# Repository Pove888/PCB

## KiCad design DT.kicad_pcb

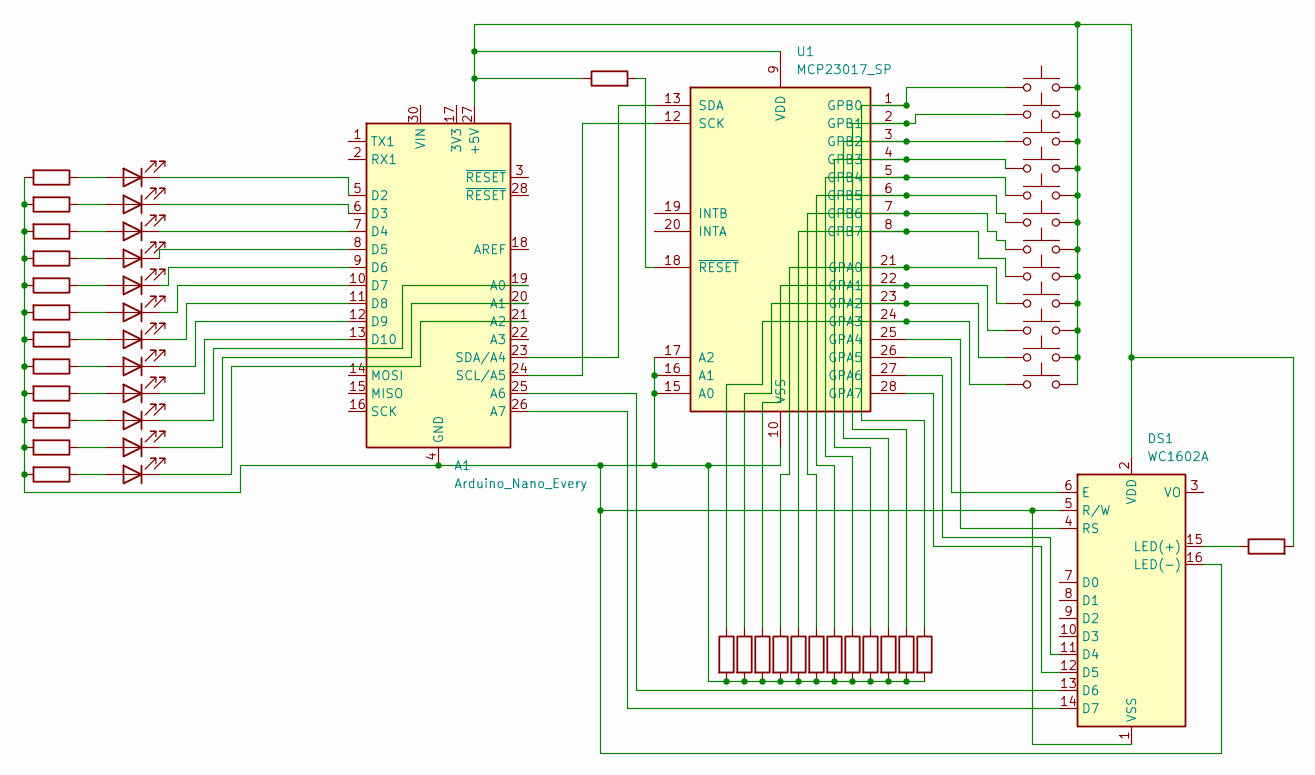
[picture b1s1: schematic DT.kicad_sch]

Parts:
A1: Arduino_Nano_Every; Arduino_Nano
D1, D2, D3, D4, D5, D6, D7, D8, D9, D10, D11, D12: LED; LED_D3.0mm
DS1: WC1602A
R1, R2, R3, R4, R5, R6, R7, R8, R9, R10, R11, R12, R13, R14, R15, R16, R17, R18, R19, R20, R21, R22, R23, R24, R25, R26: R; R_Axial_DIN0204_L3.6mm_D1.6mm_P5.08mm_Horizontal
SW1, SW2, SW3, SW4, SW5, SW6, SW7, SW8, SW9, SW10, SW11, SW12: SW_Push; SW_Cherry_MX_1.00u_PCB
U1: MCP23017_SP; DIP-28_W7.62mm

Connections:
unnamed: A1.27 (+5V), DS1.2 (VDD), R25.2, R26.1, SW1.2, SW2.2, SW3.2, SW4.2, SW5.2, SW6.2, SW7.2, SW8.2, SW9.2, SW10.2, SW11.2, SW12.2, U1.9 (VDD)
unnamed: A1.19 (A0), D3.1 (K)
unnamed: A1.20 (A1), D2.1 (K)
unnamed: A1.21 (A2), D1.1 (K)
unnamed: A1.25 (A6), DS1.13 (D6)
unnamed: A1.26 (A7), DS1.14 (D7)
unnamed: A1.5 (D2), D12.1 (K)
unnamed: A1.6 (D3), D11.1 (K)
unnamed: A1.7 (D4), D10.1 (K)
unnamed: A1.8 (D5), D9.1 (K)
unnamed: A1.9 (D6), D8.1 (K)
unnamed: A1.10 (D7), D7.1 (K)
unnamed: A1.11 (D8), D6.1 (K)
unnamed: A1.12 (D9), D5.1 (K)
unnamed: A1.13 (D10), D4.1 (K)
unnamed: A1.24 (SCL/A5), U1.12 (SCK)
unnamed: A1.23 (SDA/A4), U1.13 (SDA)
unnamed: D1.2 (A), R1.1
unnamed: D2.2 (A), R2.1
unnamed: D3.2 (A), R3.1
unnamed: D4.2 (A), R4.1
unnamed: D5.2 (A), R5.1
unnamed: D6.2 (A), R6.1
unnamed: D7.2 (A), R7.1
unnamed: D8.2 (A), R8.1
unnamed: D9.2 (A), R9.1
unnamed: D10.2 (A), R10.1
unnamed: D11.2 (A), R11.1
unnamed: D12.2 (A), R12.1
unnamed: DS1.11 (D4), U1.27 (GPA6)
unnamed: DS1.12 (D5), U1.28 (GPA7)
unnamed: DS1.6 (E), U1.26 (GPA5)
unnamed: DS1.15 (LED(+)), R25.1
unnamed: A1.4 (GND), A1.29 (GND), DS1.1 (VSS), DS1.5 (R/W), DS1.16 (LED(-)), R1.2, R2.2, R3.2, R4.2, R5.2, R6.2, R7.2, R8.2, R9.2, R10.2, R11.2, R12.2, R13.2, R14.2, R15.2, R16.2, R17.2, R18.2, R19.2, R20.2, R21.2, R22.2, R23.2, R24.2, U1.10 (VSS), U1.15 (A0), U1.16 (A1), U1.17 (A2)
unnamed: DS1.4 (RS), U1.25 (GPA4)
unnamed: R16.1, SW9.1, U1.21 (GPA0)
unnamed: R15.1, SW10.1, U1.22 (GPA1)
unnamed: R14.1, SW11.1, U1.23 (GPA2)
unnamed: R13.1, SW12.1, U1.24 (GPA3)
unnamed: R23.1, SW1.1, U1.1 (GPB0)
unnamed: R18.1, SW2.1, U1.2 (GPB1)
unnamed: R24.1, SW3.1, U1.3 (GPB2)
unnamed: R19.1, SW4.1, U1.4 (GPB3)
unnamed: R20.1, SW5.1, U1.5 (GPB4)
unnamed: R21.1, SW6.1, U1.6 (GPB5)
unnamed: R22.1, SW7.1, U1.7 (GPB6)
unnamed: R17.1, SW8.1, U1.8 (GPB7)
unnamed: R26.2, U1.18 (~RESET)

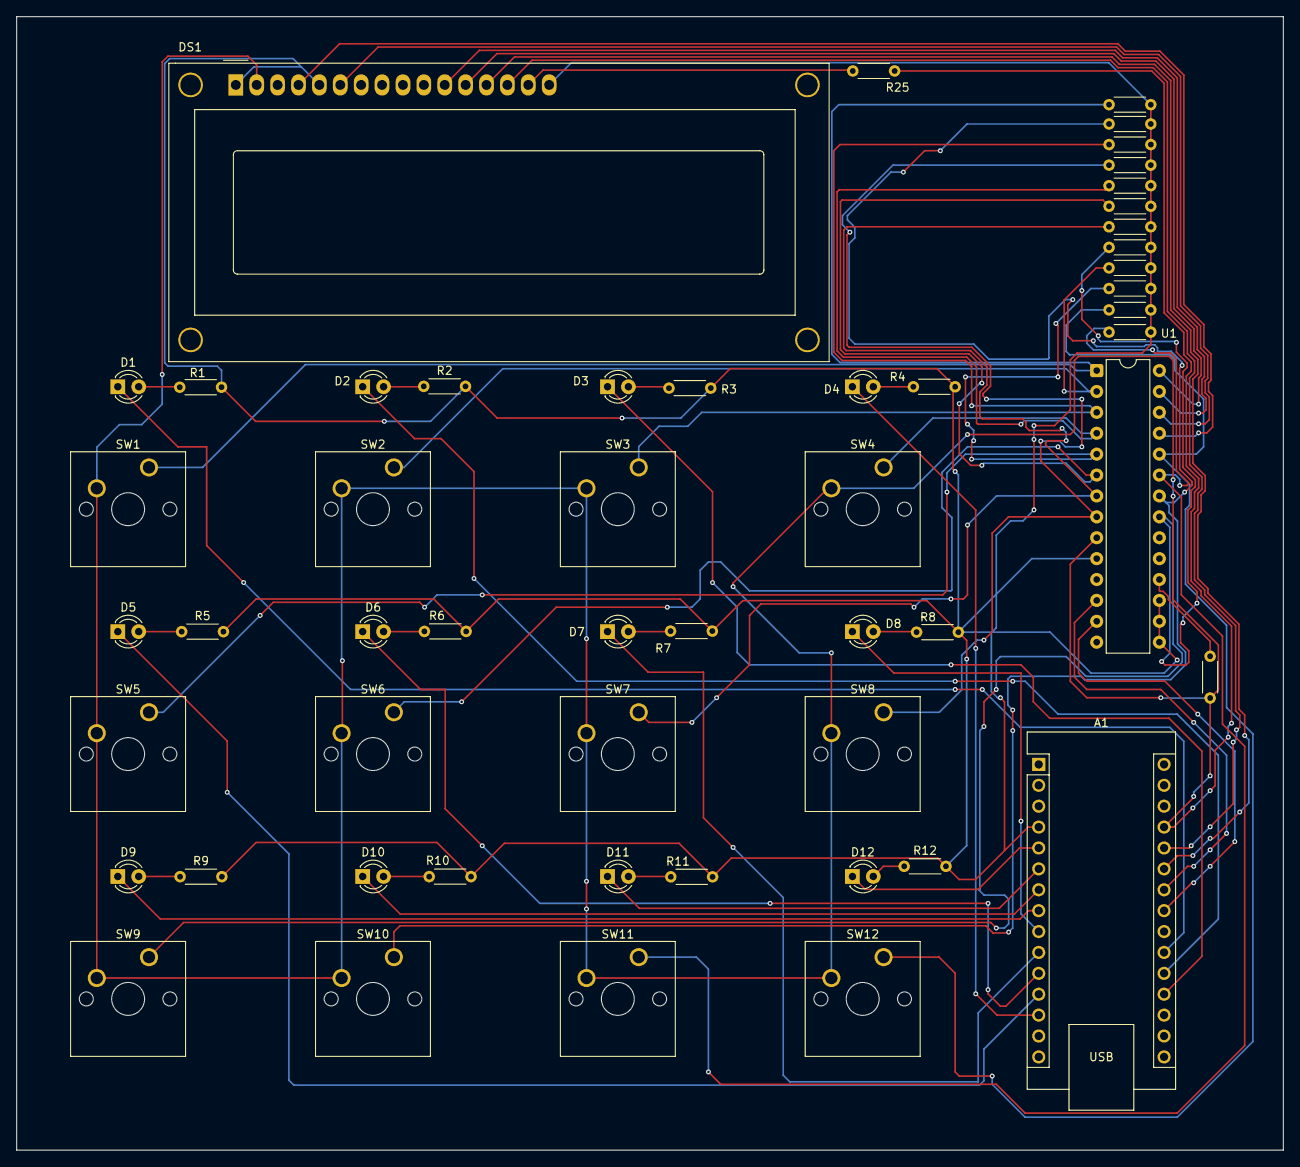
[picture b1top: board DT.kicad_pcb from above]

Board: 2 copper layers, 154.0 x 137.8 mm, 53 parts (0 on the bottom side), 48 nets.

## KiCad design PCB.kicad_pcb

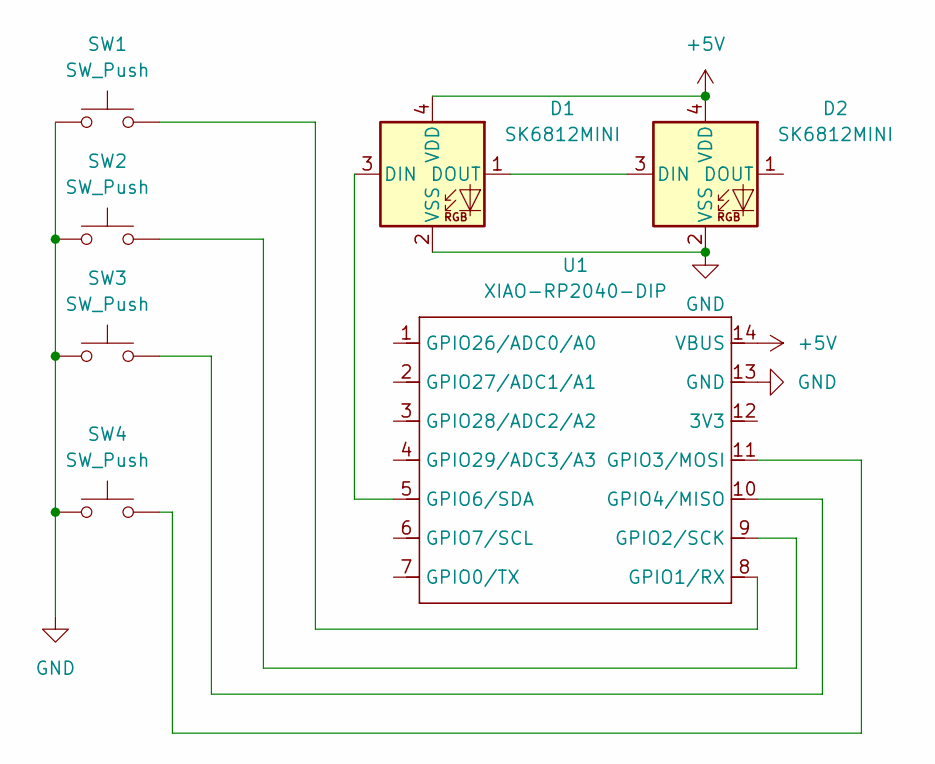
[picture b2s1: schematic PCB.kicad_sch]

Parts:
D1, D2: SK6812MINI; LED_SK6812MINI_PLCC4_3.5x3.5mm_P1.75mm
SW1, SW2, SW3, SW4: SW_Push; SW_Cherry_MX_1.00u_PCB
U1: XIAO-RP2040-DIP

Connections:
+5V: D1.4 (VDD), D2.4 (VDD), U1.14 (VBUS)
GND: D1.2 (VSS), D2.2 (VSS), SW1.1, SW2.1, SW3.1, SW4.1, U1.13 (GND)
unnamed: D1.3 (DIN), U1.5 (GPIO6/SDA)
unnamed: D1.1 (DOUT), D2.3 (DIN)
unnamed: SW1.2, U1.8 (GPIO1/RX)
unnamed: SW2.2, U1.9 (GPIO2/SCK)
unnamed: SW4.2, U1.11 (GPIO3/MOSI)
unnamed: SW3.2, U1.10 (GPIO4/MISO)

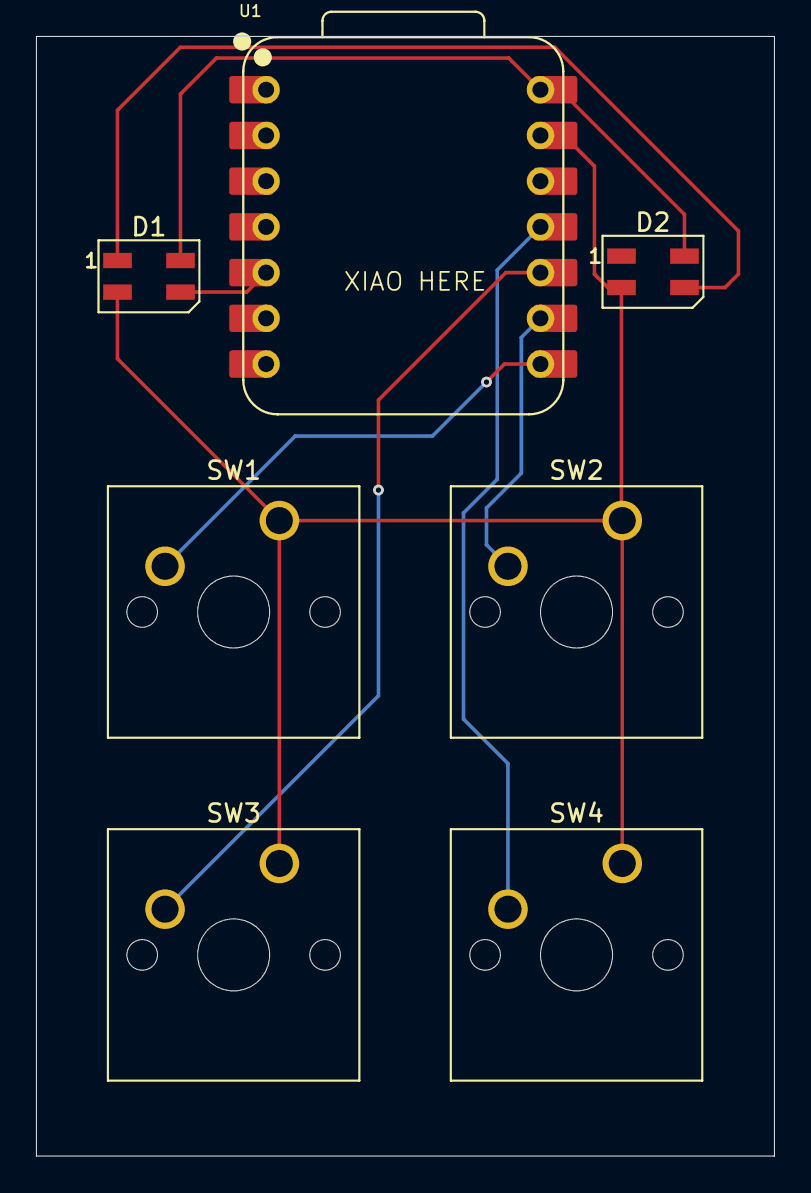
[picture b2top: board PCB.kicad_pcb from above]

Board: 2 copper layers, 41.0 x 62.2 mm, 7 parts (0 on the bottom side), 8 nets.

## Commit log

2025-12-09 added files
2025-12-09 new files
2025-12-09 started wiring
2025-12-10 more wiring
2025-12-10 finished wiring LEDs
2025-12-11 wired up mcp
2025-12-16 wirws
2025-12-17 almost finished switches
2025-12-26 finished
2025-12-26 gerbers
